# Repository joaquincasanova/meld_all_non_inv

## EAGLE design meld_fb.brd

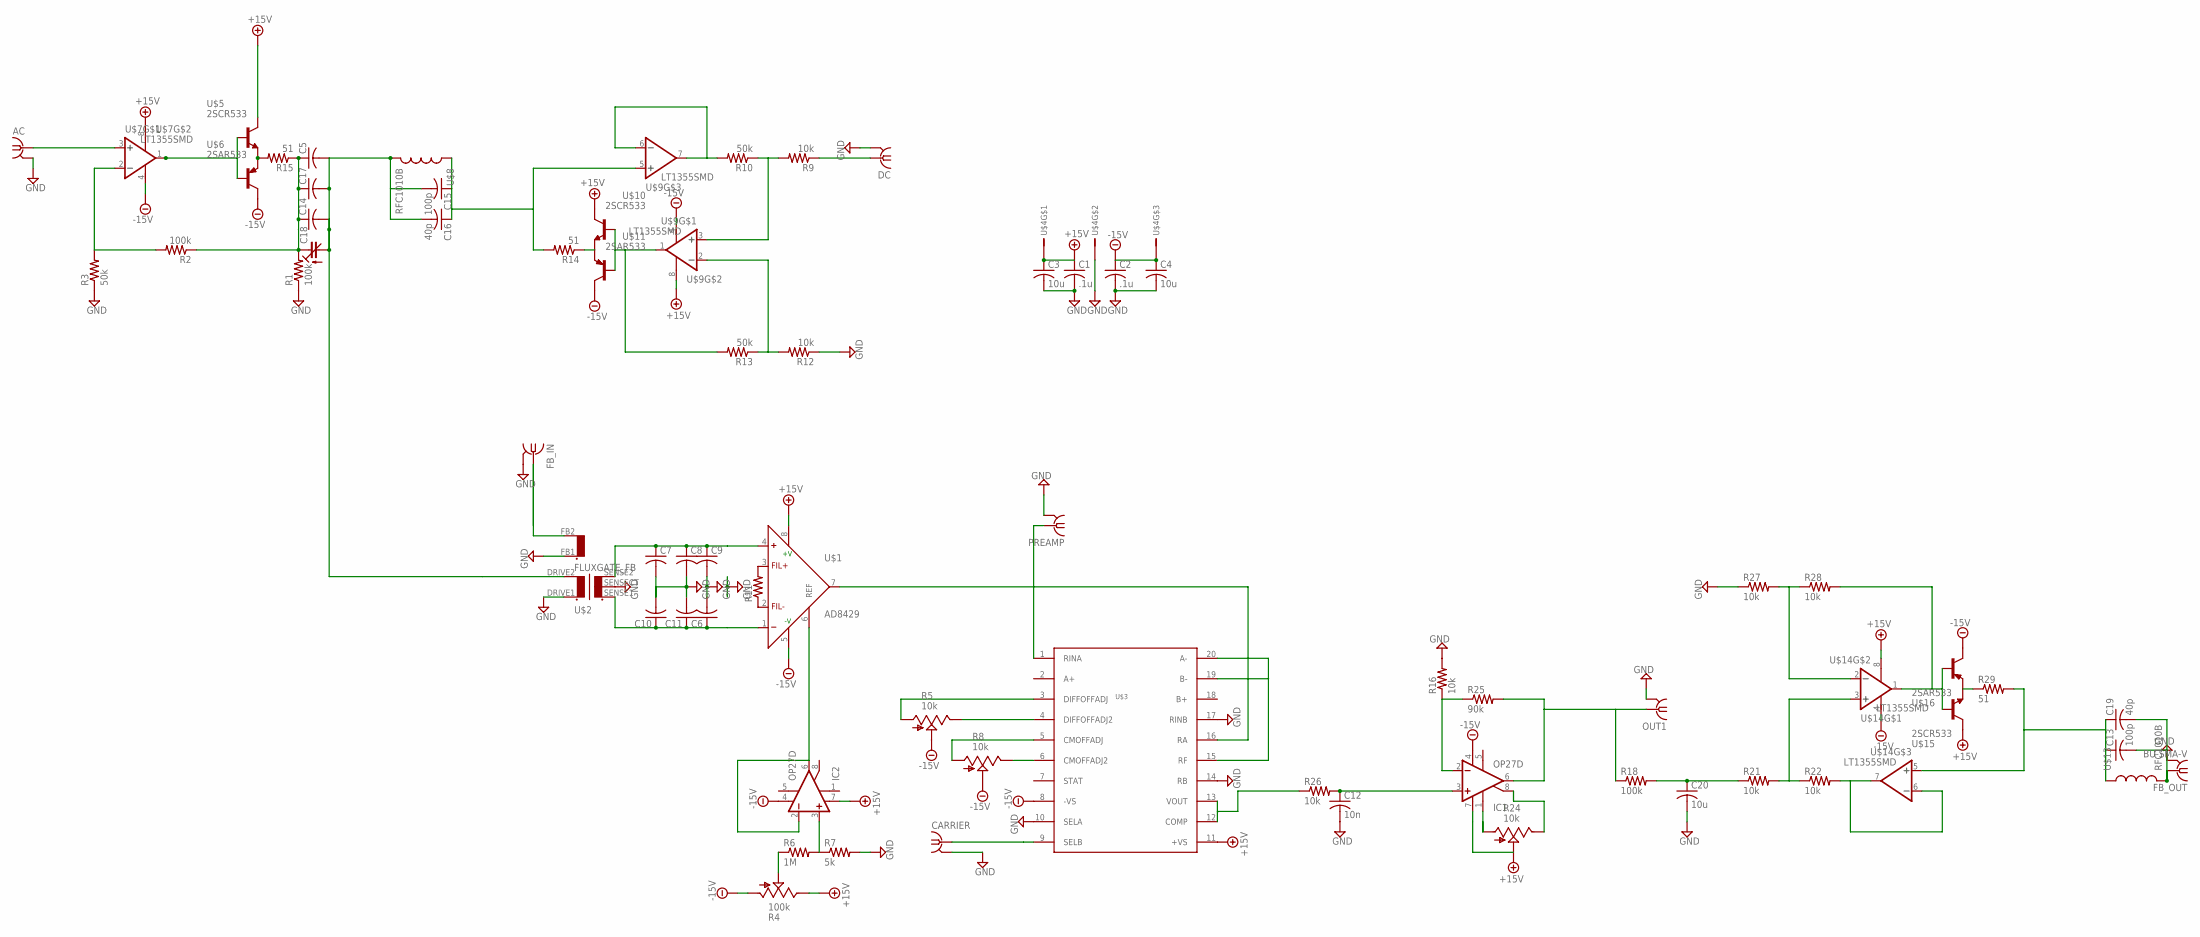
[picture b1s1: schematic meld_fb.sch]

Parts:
AC: SMA-142-0701-851/861; J502-ND-142-0701-851/861
C1, C2: .1u; C1206
C3, C4, C20: 10u; C1206
C5, C6, C7, C8, C9, C10, C11, C14, C17: C-USC0805; C0805
C12: 10n; C0805
C13, C15: 100p; C0805
C16, C19: 40p; C0805
C18: C-TRIMM; SGC3S
CARRIER: SMA-142-0701-851/861; J502-ND-142-0701-851/861
DC: SMA-142-0701-851/861; J502-ND-142-0701-851/861
FB_IN: SMA-142-0701-851/861; J502-ND-142-0701-851/861
FB_OUT: BU-SMA-V
IC1, IC2: OP27D; SO08
OUT1: SMA-142-0701-851/861; J502-ND-142-0701-851/861
PREAMP: SMA-142-0701-851/861; J502-ND-142-0701-851/861
R1, R2, R18: 100k; R0805
R3, R10, R13: 50k; R0805
R4: 100k; B64Y
R5, R8, R24: 10k; B64Y
R6: 1M; R0805
R7: 5k; R0805
R9, R12, R16, R21, R22, R26, R27, R28: 10k; R0805
R11: R-US_R0805; R0805
R14, R15, R29: 51; R2512
R25: 90k; R0805
U$1: AD8429; SO8
U$2: FLUXGATE_FB; PARA_FB
U$3: AD630; SOIC20R
U$4: B3B-AM
U$5, U$10, U$15: 2SCR533; SOT89-BCE
U$6, U$11, U$16: 2SAR533; SOT89-BCE
U$7, U$9, U$14: LT1355SMD; SOIC8
U$8, U$13: RFC1010B; 186KE

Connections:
+15V: C1.1, C3.1, IC1.7 (V+), IC2.7 (V+), R4.E, R24.S, U$1.8 (+V), U$3.11 (+VS), U$4.1, U$5.C, U$7.8 (V+), U$9.8 (V+), U$10.C, U$14.8 (V+), U$15.C
-15V: C2.1, C4.1, IC1.4 (V-), IC2.4 (V-), R4.A, R5.S, R8.S, U$1.5 (-V), U$3.8 (-VS), U$4.3, U$6.C, U$7.4 (V-), U$9.4 (V-), U$11.C, U$14.4 (V-), U$16.C
GND: AC.G@1 (2), AC.G@2 (2), AC.G@3 (2), AC.G@4 (2), C1.2, C2.2, C3.2, C4.2, C6.2, C7.2, C8.2, C9.2, C10.2, C11.2, C12.2, C20.2, CARRIER.G@1 (2), CARRIER.G@2 (2), CARRIER.G@3 (2), CARRIER.G@4 (2), DC.G@1 (2), DC.G@2 (2), DC.G@3 (2), DC.G@4 (2), FB_IN.G@1 (2), FB_IN.G@2 (2), FB_IN.G@3 (2), FB_IN.G@4 (2), FB_OUT.2, FB_OUT.3 (2), FB_OUT.4 (2), FB_OUT.5 (2), OUT1.G@1 (2), OUT1.G@2 (2), OUT1.G@3 (2), OUT1.G@4 (2), PREAMP.G@1 (2), PREAMP.G@2 (2), PREAMP.G@3 (2), PREAMP.G@4 (2), R1.1, R3.1, R7.2, R12.1, R16.2, R27.1, U$2.DRIVE1 (1), U$2.FB1 (6), U$2.SENSECT (4), U$3.10 (SELA), U$3.14 (RB), U$3.17 (RINB), U$4.2
unnamed: C7.1, C8.1, C9.1, U$1.4 (+), U$2.SENSE2 (3)
unnamed: C6.1, C10.1, C11.1, U$1.1 (-), U$2.SENSE1 (5)
unnamed: R11.2, U$1.3 (FIL+)
unnamed: PREAMP.1, U$1.7 (OUT), U$3.1 (RINA), U$3.16 (RA)
unnamed: CARRIER.1, U$3.9 (SELB)
unnamed: R15.2, U$5.E, U$6.E
unnamed: U$3.15 (RF), U$3.19 (B-), U$3.20 (A-)
unnamed: U$5.B, U$6.B, U$7.1 (OUT)
unnamed: C20.1, R18.2, R21.1
unnamed: R2.2, R3.2, U$7.2 (-IN)
unnamed: R5.A, U$3.3 (DIFFOFFADJ)
unnamed: IC2.2 (-IN), IC2.6 (OUT), U$1.6 (REF)
unnamed: IC2.3 (+IN), R6.2, R7.1
unnamed: R4.S, R6.1
unnamed: R5.E, U$3.4 (DIFFOFFADJ2)
unnamed: R8.A, U$3.5 (CMOFFADJ)
unnamed: R8.E, U$3.6 (CMOFFADJ2)
unnamed: FB_IN.1, U$2.FB2 (7)
unnamed: C5.1, C14.1, C17.1, C18.P$2 (E), R1.2, R2.1, R15.1
unnamed: AC.1, U$7.3 (+IN)
unnamed: R11.1, U$1.2 (FIL-)
unnamed: C5.2, C14.2, C15.2, C16.2, C17.2, C18.P$1 (A), U$2.DRIVE2 (2), U$8.P$2 (2)
unnamed: R14.1, U$10.E, U$11.E
unnamed: R13.2, U$9.1 (OUT), U$10.B, U$11.B
unnamed: R10.2, U$9.6 (-IN), U$9.7 (OUT)
unnamed: R9.2, R10.1, U$9.3 (+IN)
unnamed: DC.1, R9.1
unnamed: R12.2, R13.1, U$9.2 (-IN)
unnamed: C15.1, C16.1, R14.2, U$8.P$1 (1), U$9.5 (+IN)
unnamed: IC1.2 (-IN), R16.1, R25.1
unnamed: IC1.6 (OUT), OUT1.1, R18.1, R25.2
unnamed: R26.1, U$3.12 (COMP), U$3.13 (VOUT)
unnamed: C12.1, IC1.3 (+IN), R26.2
unnamed: C13.2, C19.2, FB_OUT.1, U$13.P$2 (2)
unnamed: R29.1, U$15.E, U$16.E
unnamed: R28.2, U$14.1 (OUT), U$15.B, U$16.B
unnamed: R22.2, U$14.6 (-IN), U$14.7 (OUT)
unnamed: IC1.1 (ON1), R24.A
unnamed: IC1.8 (ON2), R24.E
unnamed: R21.2, R22.1, U$14.3 (+IN)
unnamed: R27.2, R28.1, U$14.2 (-IN)
unnamed: C13.1, C19.1, R29.2, U$13.P$1 (1), U$14.5 (+IN)

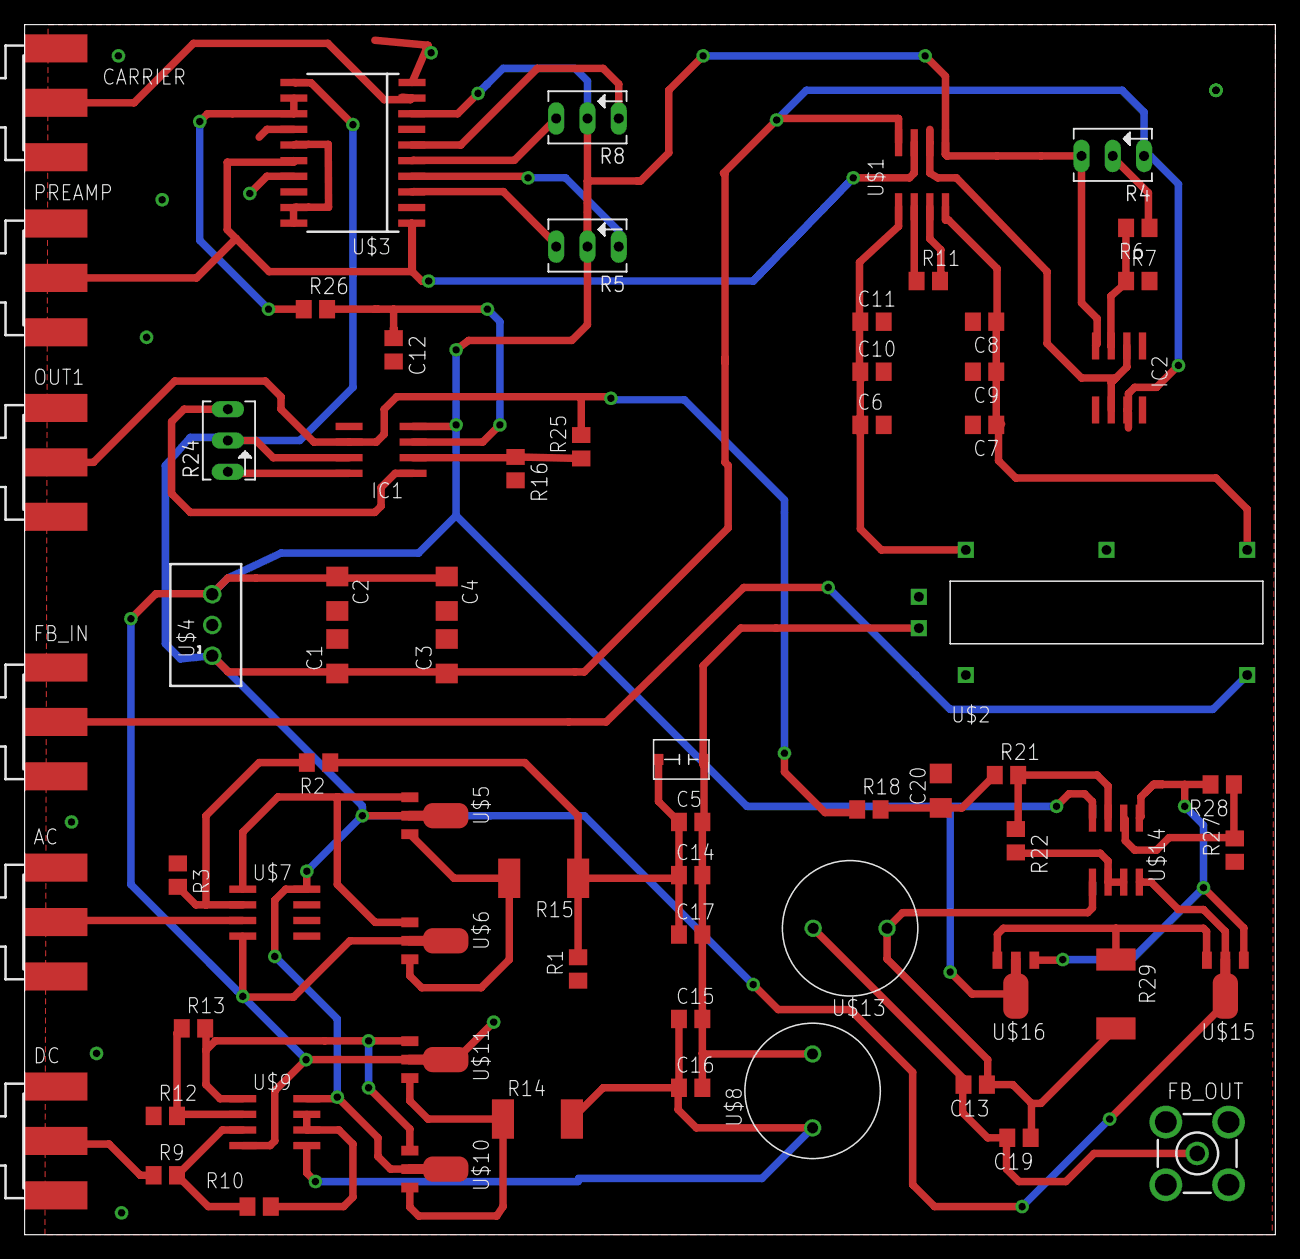
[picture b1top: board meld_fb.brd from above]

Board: 2 copper layers, 101.6 x 98.3 mm, 69 parts (0 on the bottom side), 45 nets.

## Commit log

2017-01-31 first
